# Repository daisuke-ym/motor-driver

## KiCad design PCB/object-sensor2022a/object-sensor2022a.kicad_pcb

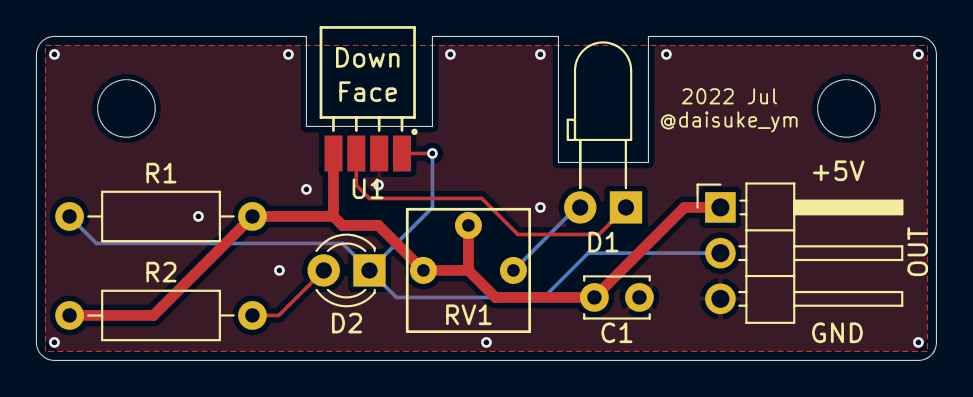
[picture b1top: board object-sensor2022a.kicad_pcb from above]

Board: 2 copper layers, 50.0 x 18.0 mm, 10 parts (0 on the bottom side), 6 nets.

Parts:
C1: 0.1u; C_Disc_D3.4mm_W2.1mm_P2.50mm
D1: IR LED; LED_D3.0mm_Horizontal_O3.81mm_Z6.0mm
D2: YELLOW; LED_D3.0mm_Clear
J1: Conn_01x03; PinHeader_1x03_P2.54mm_Horizontal
MH1, MH2: MountingHole_3.2mm_M3
R1: 10k; R_Axial_DIN0207_L6.3mm_D2.5mm_P10.16mm_Horizontal
R2: 1k; R_Axial_DIN0207_L6.3mm_D2.5mm_P10.16mm_Horizontal
RV1: 4K7; GF063P1
U1: S6809; S6809_Horizontal_Facedown

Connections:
+5V: C1.1, J1.1, R1.2, R2.1, RV1.1, RV1.2, U1.4
/WS1: D2.1, J1.2, R1.1, U1.1
GND: C1.2, J1.3, U1.2
unnamed: D1.1, U1.3
unnamed: D1.2, RV1.3
unnamed: D2.2, R2.2

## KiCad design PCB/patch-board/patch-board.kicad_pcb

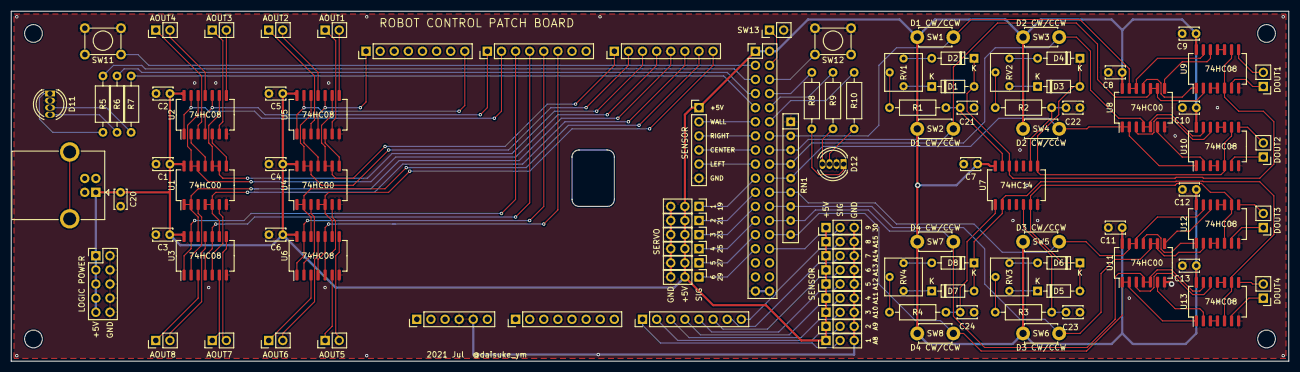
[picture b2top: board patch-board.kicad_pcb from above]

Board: 2 copper layers, 230.0 x 63.0 mm, 104 parts (0 on the bottom side), 128 nets.

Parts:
C1, C2, C3, C4, C5, C6, C7, C8, C9, C10, C11, C12, C13, C20, C21, C22, C23, C24: 0.1u; C_Disc_D3.4mm_W2.1mm_P2.50mm
D1, D2, D3, D4, D5, D6, D7, D8: 1N4148; D_DO-35_SOD27_P7.62mm_Horizontal
D11, D12: LED_RCBG; LED_D5.0mm-4_RGB
J1: USB_B; USB_B_OST_USB-B1HSxx_Horizontal
J2: LOGIC POWER SUPPLY; PinHeader_2x05_P2.54mm_Vertical
J3: MEGA_13-8; PinHeader_1x08_P2.54mm_Vertical
J4: MEGA_7-0; PinHeader_1x08_P2.54mm_Vertical
J5: MEGA_14-21; PinHeader_1x08_P2.54mm_Vertical
J6: MEGA_A8-A15; PinHeader_1x08_P2.54mm_Vertical
J7: MEGA_A0-A7; PinHeader_1x08_P2.54mm_Vertical
J8: MEGA_POWER; PinHeader_1x06_P2.54mm_Vertical
J9: MEGA_22-53; PinHeader_2x18_P2.54mm_Vertical
J11: AOUT1; PinHeader_1x02_P2.54mm_Vertical
J12: AOUT2; PinHeader_1x02_P2.54mm_Vertical
J13: AOUT3; PinHeader_1x02_P2.54mm_Vertical
J14: AOUT4; PinHeader_1x02_P2.54mm_Vertical
J15: AOUT5; PinHeader_1x02_P2.54mm_Vertical
J16: AOUT6; PinHeader_1x02_P2.54mm_Vertical
J17: AOUT7; PinHeader_1x02_P2.54mm_Vertical
J18: AOUT8; PinHeader_1x02_P2.54mm_Vertical
J21: DIGITAL OUT1; PinHeader_1x02_P2.54mm_Vertical
J22: DIGITAL OUT2; PinHeader_1x02_P2.54mm_Vertical
J23: DIGITAL OUT3; PinHeader_1x02_P2.54mm_Vertical
J24: DIGITAL OUT4; PinHeader_1x02_P2.54mm_Vertical
J31: S01; PinHeader_1x03_P2.54mm_Vertical
J32: S02; PinHeader_1x03_P2.54mm_Vertical
J33: S03; PinHeader_1x03_P2.54mm_Vertical
J34: S04; PinHeader_1x03_P2.54mm_Vertical
J35: S05; PinHeader_1x03_P2.54mm_Vertical
J36: S06; PinHeader_1x03_P2.54mm_Vertical
J37: S07; PinHeader_1x03_P2.54mm_Vertical
J38: S08; PinHeader_1x03_P2.54mm_Vertical
J39: S09; PinHeader_1x03_P2.54mm_Vertical
J40: S10; PinHeader_1x06_P2.54mm_Vertical
J41, J42, J43, J44, J45, J46: SV; PinHeader_1x03_P2.54mm_Vertical
R1, R2, R3, R4: R; R_Axial_DIN0207_L6.3mm_D2.5mm_P10.16mm_Horizontal
R5, R6, R7, R8, R9, R10: 1k; R_Axial_DIN0207_L6.3mm_D2.5mm_P10.16mm_Horizontal
RN1: 330; R_Array_SIP9
RV1, RV2, RV3, RV4: R_POT; GF063P1
SW1: D1A; TactSW_TVBP06_3.5x6.0-ThroughHole
SW2: D1B; TactSW_TVBP06_3.5x6.0-ThroughHole
SW3: D2A; TactSW_TVBP06_3.5x6.0-ThroughHole
SW4: D2B; TactSW_TVBP06_3.5x6.0-ThroughHole
SW5: D3A; TactSW_TVBP06_3.5x6.0-ThroughHole
SW6: D3B; TactSW_TVBP06_3.5x6.0-ThroughHole
SW7: D4A; TactSW_TVBP06_3.5x6.0-ThroughHole
SW8: D4B; TactSW_TVBP06_3.5x6.0-ThroughHole
SW11, SW12: SW_DPST; DTS-6-V-2
SW13: Conn_01x02; PinHeader_1x02_P2.54mm_Vertical
U1, U4, U8, U11: 74HC00; SO-14_5.3x10.2mm_P1.27mm
U2, U3, U5, U6, U9, U10, U12, U13: 74HC08; SO-14_5.3x10.2mm_P1.27mm
U7: 74HC14; SO-14_5.3x10.2mm_P1.27mm

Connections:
+5V: C1.1, C2.1, C3.1, C4.1, C5.1, C6.1, C7.1, C8.1, C9.1, C10.1, C11.1, C12.1, C13.1, C20.1, J1.1, J2.1, J2.3, J2.5, J2.7, J2.9, J9.1, J9.2, J31.1, J32.1, J33.1, J34.1, J35.1, J36.1, J37.1, J38.1, J39.1, J40.1, J41.2, J42.2, J43.2, J44.2, J45.2, J46.2, SW1.1, SW2.1, SW3.1, SW4.1, SW5.1, SW6.1, SW7.1, SW8.1, U1.14, U2.14, U3.14, U4.14, U5.14, U6.14, U7.14, U8.14, U9.14, U10.14, U11.14, U12.14, U13.14
/AOUT1A: J11.2, U5.8
/AOUT1B: J11.1, U5.6
/AOUT2A: J12.2, U5.11
/AOUT2B: J12.1, U5.3
/AOUT3A: J13.2, U2.8
/AOUT3B: J13.1, U2.6
/AOUT4A: J14.2, U2.11
/AOUT4B: J14.1, U2.3
/AOUT5A: J15.2, U3.11
/AOUT5B: J15.1, U3.3
/AOUT6A: J16.2, U3.8
/AOUT6B: J16.1, U3.6
/AOUT7A: J17.2, U6.11
/AOUT7B: J17.1, U6.3
/AOUT8A: J18.2, U6.8
/AOUT8B: J18.1, U6.6
/CSENSOR: J9.15, J40.4
/DIN1A: J9.14, RN1.2, SW1.2, U8.12, U8.13, U9.13
/DIN1B: J9.16, RN1.3, SW2.2, U8.9, U8.10, U9.2
/DIN2A: J9.18, RN1.4, SW3.2, U8.4, U8.5, U10.13
/DIN2B: J9.20, RN1.5, SW4.2, U8.1, U8.2, U10.1
/DIN3A: J9.22, RN1.6, SW5.2, U11.12, U11.13, U12.13
/DIN3B: J9.24, RN1.7, SW6.2, U11.9, U11.10, U12.2
/DIN4A: J9.26, RN1.8, SW7.2, U11.4, U11.5, U13.13
/DIN4B: J9.28, RN1.9, SW8.2, U11.1, U11.2, U13.1
/DOUT1A: J21.1, U9.6
/DOUT1B: J21.2, U9.8
/DOUT2A: J22.1, U10.6
/DOUT2B: J22.2, U10.8
/DOUT3A: J23.1, U12.6
/DOUT3B: J23.2, U12.8
/DOUT4A: J24.1, U13.6
/DOUT4B: J24.2, U13.8
/LED1B: J9.9, R7.2
/LED1G: J9.7, R6.2
/LED1R: J9.5, R5.2
/LED2B: J9.12, R10.2
/LED2G: J9.10, R9.2
/LED2R: J9.8, R8.2
/LSENSOR: J9.17, J40.5
/OSC1: D1.2, D2.1, U7.12, U9.5, U9.9
/OSC2: D3.2, D4.1, U7.8, U10.5, U10.9
/OSC3: D5.2, D6.1, U7.6, U12.5, U12.9
/OSC4: D7.2, D8.1, U7.2, U13.5, U13.9
/PWM1IN: J3.1, U5.4, U5.10
/PWM2IN: J3.8, U5.1, U5.13
/PWM3IN: J4.1, U2.4, U2.10
/PWM4IN: J4.2, U2.1, U2.13
/PWM5IN: J4.3, U3.1, U3.13
/PWM6IN: J4.4, U3.4, U3.10
/PWM7IN: J4.5, U6.1, U6.13
/PWM8IN: J4.6, U6.4, U6.10
/RSENSOR: J9.13, J40.3
/SEL1: J5.1, U4.9, U4.10, U5.9
/SEL2: J5.2, U4.12, U4.13, U5.12
/SEL3: J5.3, U1.9, U1.10, U2.9
/SEL4: J5.4, U1.12, U1.13, U2.12
/SEL5: J5.5, U1.1, U1.2, U3.12
/SEL6: J5.6, U1.4, U1.5, U3.9
/SEL7: J5.7, U4.1, U4.2, U6.12
/SEL8: J5.8, U4.4, U4.5, U6.9
/SENSOR01: J6.1, J31.2
/SENSOR02: J6.2, J32.2
/SENSOR03: J6.3, J33.2
/SENSOR04: J6.4, J34.2
/SENSOR05: J6.5, J35.2
/SENSOR06: J6.6, J36.2
/SENSOR07: J6.7, J37.2
/SENSOR08: J6.8, J38.2
/SENSOR09: J9.30, J39.2
/SV1: J9.19, J41.1
/SV2: J9.21, J42.1
/SV3: J9.23, J43.1
/SV4: J9.25, J44.1
/SV5: J9.27, J45.1
/SV6: J9.29, J46.1
/SW11: J9.3, SW11.1, SW11.3
/SW12: J9.6, SW12.1, SW12.3
/SW13: J9.4, SW13.1
/WSENSOR: J9.11, J40.2
GND: C1.2, C2.2, C3.2, C4.2, C5.2, C6.2, C7.2, C8.2, C9.2, C10.2, C11.2, C12.2, C13.2, C20.2, C21.2, C22.2, C23.2, C24.2, D11.2, D12.2, J1.4, J2.2, J2.4, J2.6, J2.8, J2.10, J8.4, J8.5, J9.35, J9.36, J31.3, J32.3, J33.3, J34.3, J35.3, J36.3, J37.3, J38.3, J39.3, J40.6, J41.3, J42.3, J43.3, J44.3, J45.3, J46.3, RN1.1, SW11.2, SW11.4, SW12.2, SW12.4, SW13.2, U1.7, U2.7, U3.7, U4.7, U5.7, U6.7, U7.3, U7.7, U7.11, U8.7, U9.7, U10.7, U11.7, U12.7, U13.7
unnamed: C21.1, R1.2, U7.13
unnamed: C22.1, R2.2, U7.9
unnamed: C23.1, R3.2, U7.5
unnamed: C24.1, R4.2, U7.1
unnamed: D1.1, RV1.1
unnamed: D2.2, RV1.3
unnamed: D3.1, RV2.1
unnamed: D4.2, RV2.3
unnamed: D5.1, RV3.1
unnamed: D6.2, RV3.3
unnamed: D7.1, RV4.1
unnamed: D8.2, RV4.3
unnamed: D11.1, R5.1
unnamed: D11.3, R7.1
unnamed: D11.4, R6.1
unnamed: D12.1, R8.1
unnamed: D12.3, R10.1
unnamed: D12.4, R9.1
unnamed: R1.1, RV1.2
unnamed: R2.1, RV2.2
unnamed: R3.1, RV3.2
unnamed: R4.1, RV4.2
unnamed: U1.3, U3.2
unnamed: U1.6, U3.5
unnamed: U1.8, U2.5
unnamed: U1.11, U2.2
unnamed: U4.3, U6.2
unnamed: U4.6, U6.5
unnamed: U4.8, U5.5
unnamed: U4.11, U5.2
unnamed: U8.8, U9.12
unnamed: U8.11, U9.1
unnamed: U9.3, U9.4
unnamed: U9.10, U9.11
unnamed: U8.6, U10.2
unnamed: U10.3, U10.4
unnamed: U10.10, U10.11
unnamed: U8.3, U10.12
unnamed: U11.3, U13.12
unnamed: U11.6, U13.2
unnamed: U11.8, U12.12
unnamed: U11.11, U12.1
unnamed: U12.3, U12.4
unnamed: U12.10, U12.11
unnamed: U13.3, U13.4
unnamed: U13.10, U13.11

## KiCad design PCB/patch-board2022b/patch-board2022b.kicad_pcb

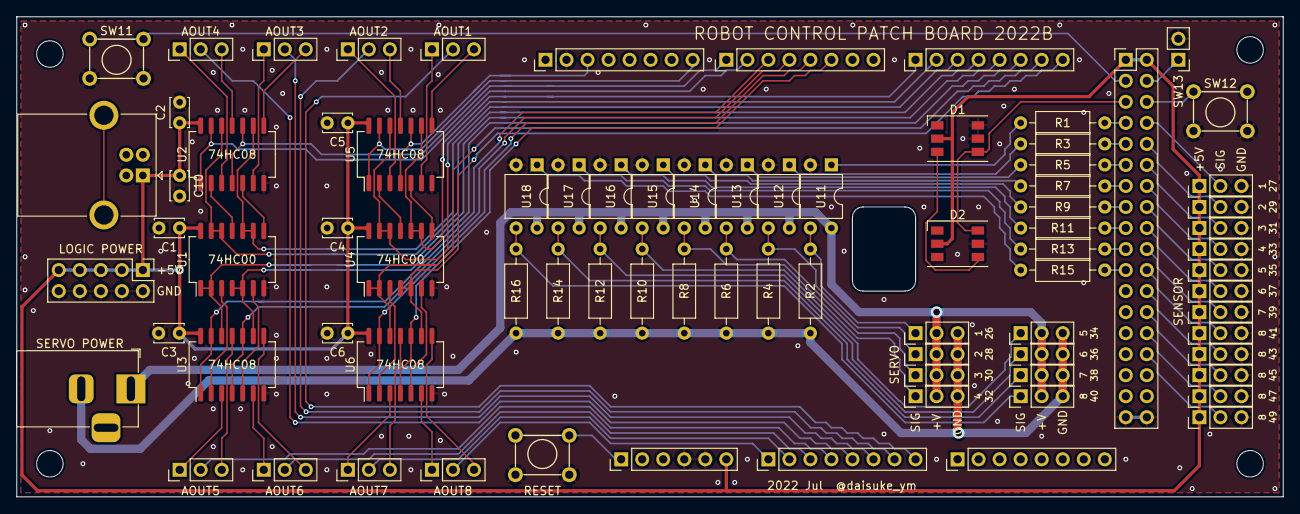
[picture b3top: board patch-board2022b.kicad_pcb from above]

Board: 2 copper layers, 153.0 x 58.0 mm, 81 parts (0 on the bottom side), 94 nets.

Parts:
C1, C2, C3, C4, C5, C6, C10: 0.1u; C_Disc_D3.4mm_W2.1mm_P2.50mm
D1, D2: WS2813; LED_WS2812_PLCC6_5.0x5.0mm_P1.6mm
J1: USB_B; USB_B_OST_USB-B1HSxx_Horizontal
J2: LOGIC POWER SUPPLY; PinHeader_2x05_P2.54mm_Vertical
J3: MEGA_13-8; PinHeader_1x08_P2.54mm_Vertical
J4: MEGA_7-0; PinHeader_1x08_P2.54mm_Vertical
J5: MEGA_14-21; PinHeader_1x08_P2.54mm_Vertical
J6: MEGA_A8-A15; PinHeader_1x08_P2.54mm_Vertical
J7: MEGA_A0-A7; PinHeader_1x08_P2.54mm_Vertical
J8: MEGA_POWER; PinHeader_1x06_P2.54mm_Vertical
J9: MEGA_22-53; PinHeader_2x18_P2.54mm_Vertical
J10: SERVO POWER SUPPLY; BarrelJack_Horizontal
J11: AOUT1; PinHeader_1x03_P2.54mm_Vertical
J12: AOUT2; PinHeader_1x03_P2.54mm_Vertical
J13: AOUT3; PinHeader_1x03_P2.54mm_Vertical
J14: AOUT4; PinHeader_1x03_P2.54mm_Vertical
J15: AOUT5; PinHeader_1x03_P2.54mm_Vertical
J16: AOUT6; PinHeader_1x03_P2.54mm_Vertical
J17: AOUT7; PinHeader_1x03_P2.54mm_Vertical
J18: AOUT8; PinHeader_1x03_P2.54mm_Vertical
J21, J22, J23, J24, J25, J26, J27, J28: SV; PinHeader_1x03_P2.54mm_Vertical
J31: S01; PinHeader_1x03_P2.54mm_Vertical
J32: S02; PinHeader_1x03_P2.54mm_Vertical
J33: S03; PinHeader_1x03_P2.54mm_Vertical
J34: S04; PinHeader_1x03_P2.54mm_Vertical
J35: S05; PinHeader_1x03_P2.54mm_Vertical
J36: S06; PinHeader_1x03_P2.54mm_Vertical
J37: S07; PinHeader_1x03_P2.54mm_Vertical
J38: S08; PinHeader_1x03_P2.54mm_Vertical
J39: S09; PinHeader_1x03_P2.54mm_Vertical
J40: S10; PinHeader_1x03_P2.54mm_Vertical
J41: S11; PinHeader_1x03_P2.54mm_Vertical
J42: S12; PinHeader_1x03_P2.54mm_Vertical
R1, R2, R3, R4, R5, R6, R7, R8, R9, R10, R11, R12, R13, R14, R15, R16: 330; R_Axial_DIN0207_L6.3mm_D2.5mm_P10.16mm_Horizontal
SW1: RESET; DTS-6-V-2
SW11, SW12: SW_DPST; DTS-6-V-2
SW13: Conn_01x02; PinHeader_1x02_P2.54mm_Vertical
U1, U4: 74HC00; SO-14_5.3x10.2mm_P1.27mm
U2, U3, U5, U6: 74HC08; SO-14_5.3x10.2mm_P1.27mm
U11, U12, U13, U14, U15, U16, U17, U18: TLP785; DIP-4_W7.62mm

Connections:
+5V: C1.1, C2.1, C3.1, C4.1, C5.1, C6.1, C10.1, D1.2, D2.2, J1.1, J2.1, J2.3, J2.5, J2.7, J2.9, J8.6, J9.1, J9.2, J31.1, J32.1, J33.1, J34.1, J35.1, J36.1, J37.1, J38.1, J39.1, J40.1, J41.1, J42.1, U1.14, U2.14, U3.14, U4.14, U5.14, U6.14
+6V: J10.1, J21.2, J22.2, J23.2, J24.2, J25.2, J26.2, J27.2, J28.2, U11.4, U12.4, U13.4, U14.4, U15.4, U16.4, U17.4, U18.4
/AOUT1A: J11.3, U5.8
/AOUT1B: J11.1, U5.6
/AOUT1M: J7.8, J11.2
/AOUT2A: J12.3, U5.11
/AOUT2B: J12.1, U5.3
/AOUT2M: J7.7, J12.2
/AOUT3A: J13.3, U2.8
/AOUT3B: J13.1, U2.6
/AOUT3M: J7.6, J13.2
/AOUT4A: J14.3, U2.11
/AOUT4B: J14.1, U2.3
/AOUT4M: J7.5, J14.2
/AOUT5A: J15.3, U3.11
/AOUT5B: J15.1, U3.3
/AOUT5M: J7.4, J15.2
/AOUT6A: J16.3, U3.8
/AOUT6B: J16.1, U3.6
/AOUT6M: J7.3, J16.2
/AOUT7A: J17.3, U6.11
/AOUT7B: J17.1, U6.3
/AOUT7M: J7.2, J17.2
/AOUT8A: J18.3, U6.8
/AOUT8B: J18.1, U6.6
/AOUT8M: J7.1, J18.2
/LED1: D1.4, D2.6, J9.5
/PWM1IN: J3.3, U5.4, U5.10
/PWM2IN: J3.8, U5.1, U5.13
/PWM3IN: J4.1, U2.4, U2.10
/PWM4IN: J4.2, U2.1, U2.13
/PWM5IN: J4.3, U3.1, U3.13
/PWM6IN: J4.4, U3.4, U3.10
/PWM7IN: J4.5, U6.1, U6.13
/PWM8IN: J4.6, U6.4, U6.10
/SEL1: J5.1, U4.9, U4.10, U5.9
/SEL2: J5.2, U4.12, U4.13, U5.12
/SEL3: J5.3, U1.9, U1.10, U2.9
/SEL4: J5.4, U1.12, U1.13, U2.12
/SEL5: J5.5, U1.1, U1.2, U3.12
/SEL6: J5.6, U1.4, U1.5, U3.9
/SEL7: J5.7, U4.1, U4.2, U6.12
/SEL8: J5.8, U4.4, U4.5, U6.9
/SENSOR1: J9.8, J31.2
/SENSOR2: J9.10, J32.2
/SENSOR3: J9.12, J33.2
/SENSOR4: J9.14, J34.2
/SENSOR5: J9.16, J35.2
/SENSOR6: J9.18, J36.2
/SENSOR7: J9.20, J37.2
/SENSOR8: J9.22, J38.2
/SENSOR9: J9.24, J39.2
/SENSOR10: J9.26, J40.2
/SENSOR11: J9.28, J41.2
/SENSOR12: J9.30, J42.2
/SV1: J21.1, R2.2, U11.3
/SV1IN: J9.7, R1.2
/SV2: J22.1, R4.2, U12.3
/SV2IN: J9.9, R3.2
/SV3: J23.1, R6.2, U13.3
/SV3IN: J9.11, R5.2
/SV4: J24.1, R8.2, U14.3
/SV4IN: J9.13, R7.2
/SV5: J25.1, R10.2, U15.3
/SV5IN: J9.15, R9.2
/SV6: J26.1, R12.2, U16.3
/SV6IN: J9.17, R11.2
/SV7: J27.1, R14.2, U17.3
/SV7IN: J9.19, R13.2
/SV8: J28.1, R16.2, U18.3
/SV8IN: J9.21, R15.2
/SW11: J9.3, SW11.1, SW11.3
/SW12: J9.6, SW12.1, SW12.3
/SW13: J9.4, SW13.1
GND: C1.2, C2.2, C3.2, C4.2, C5.2, C6.2, C10.2, D1.5, D1.6, D2.5, J1.4, J2.2, J2.4, J2.6, J2.8, J2.10, J3.2, J8.4, J8.5, J9.35, J9.36, J31.3, J32.3, J33.3, J34.3, J35.3, J36.3, J37.3, J38.3, J39.3, J40.3, J41.3, J42.3, SW1.1, SW1.3, SW11.2, SW11.4, SW12.2, SW12.4, SW13.2, U1.7, U2.7, U3.7, U4.7, U5.7, U6.7, U11.2, U12.2, U13.2, U14.2, U15.2, U16.2, U17.2, U18.2
GNDPWR: J10.2, J21.3, J22.3, J23.3, J24.3, J25.3, J26.3, J27.3, J28.3, R2.1, R4.1, R6.1, R8.1, R10.1, R12.1, R14.1, R16.1
unnamed: D1.3, D2.4
unnamed: J8.1, SW1.2, SW1.4
unnamed: R1.1, U11.1
unnamed: R3.1, U12.1
unnamed: R5.1, U13.1
unnamed: R7.1, U14.1
unnamed: R9.1, U15.1
unnamed: R11.1, U16.1
unnamed: R13.1, U17.1
unnamed: R15.1, U18.1
unnamed: U1.3, U3.2
unnamed: U1.6, U3.5
unnamed: U1.8, U2.5
unnamed: U1.11, U2.2
unnamed: U4.3, U6.2
unnamed: U4.6, U6.5
unnamed: U4.8, U5.5
unnamed: U4.11, U5.2

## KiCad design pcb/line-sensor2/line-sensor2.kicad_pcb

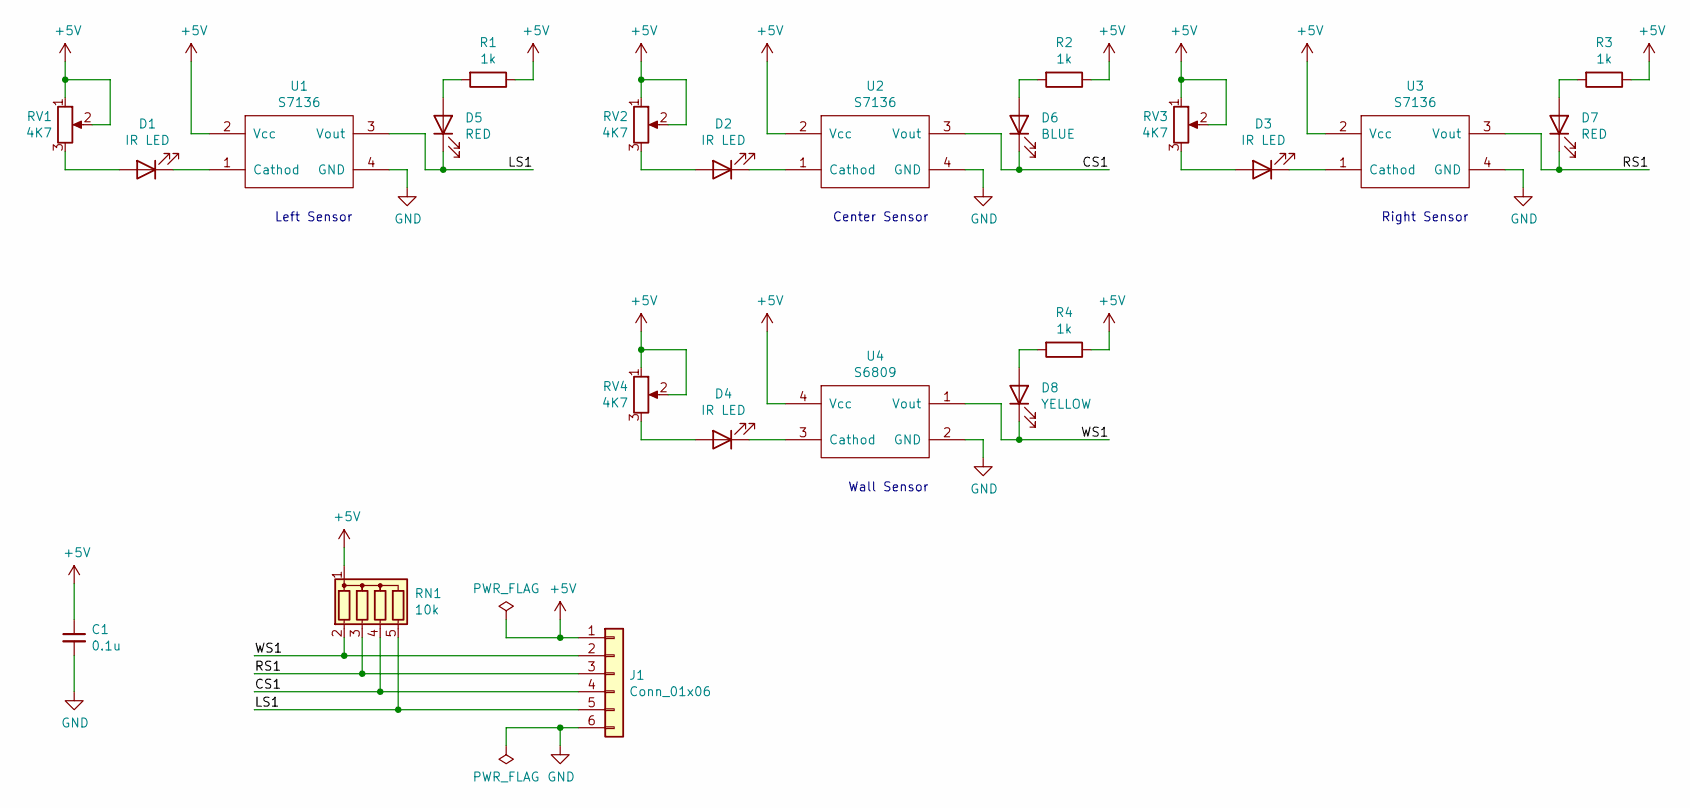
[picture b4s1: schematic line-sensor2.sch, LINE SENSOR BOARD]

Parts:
C1: 0.1u; C_Disc_D3.4mm_W2.1mm_P2.50mm
D1, D2, D3: IR LED; LED_D3.0mm_Clear
D4: IR LED; LED_D3.0mm_Horizontal_O3.81mm_Z6.0mm
D5, D7: RED; LED_D3.0mm_Clear
D6: BLUE; LED_D3.0mm_Clear
D8: YELLOW; LED_D3.0mm_Clear
J1: Conn_01x06; PinHeader_1x06_P2.54mm_Horizontal
R1, R2, R3, R4: 1k; R_Axial_DIN0207_L6.3mm_D2.5mm_P10.16mm_Horizontal
RN1: 10k; R_Array_SIP5
RV1, RV2, RV3, RV4: 4K7; GF063P1
U1, U2, U3: S7136
U4: S6809; S6809_Horizontal_Facedown

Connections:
+5V: C1.1, J1.1, R1.1, R2.1, R3.1, R4.1, RN1.1 (common), RV1.1, RV1.2, RV2.1, RV2.2, RV3.1, RV3.2, RV4.1, RV4.2, U1.2 (Vcc), U2.2 (Vcc), U3.2 (Vcc), U4.4 (Vcc)
/CS1: D6.1 (K), J1.4, RN1.4 (R3), U2.3 (Vout)
/LS1: D5.1 (K), J1.5, RN1.5 (R4), U1.3 (Vout)
/RS1: D7.1 (K), J1.3, RN1.3 (R2), U3.3 (Vout)
/WS1: D8.1 (K), J1.2, RN1.2 (R1), U4.1 (Vout)
GND: C1.2, J1.6, U1.4 (GND), U2.4 (GND), U3.4 (GND), U4.2 (GND)
unnamed: D1.1 (K), U1.1 (Cathod)
unnamed: D1.2 (A), RV1.3
unnamed: D2.1 (K), U2.1 (Cathod)
unnamed: D2.2 (A), RV2.3
unnamed: D3.1 (K), U3.1 (Cathod)
unnamed: D3.2 (A), RV3.3
unnamed: D4.1 (K), U4.3 (Cathod)
unnamed: D4.2 (A), RV4.3
unnamed: D5.2 (A), R1.2
unnamed: D6.2 (A), R2.2
unnamed: D7.2 (A), R3.2
unnamed: D8.2 (A), R4.2

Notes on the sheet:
Wall Sensor
Left Sensor
Center Sensor
Right Sensor

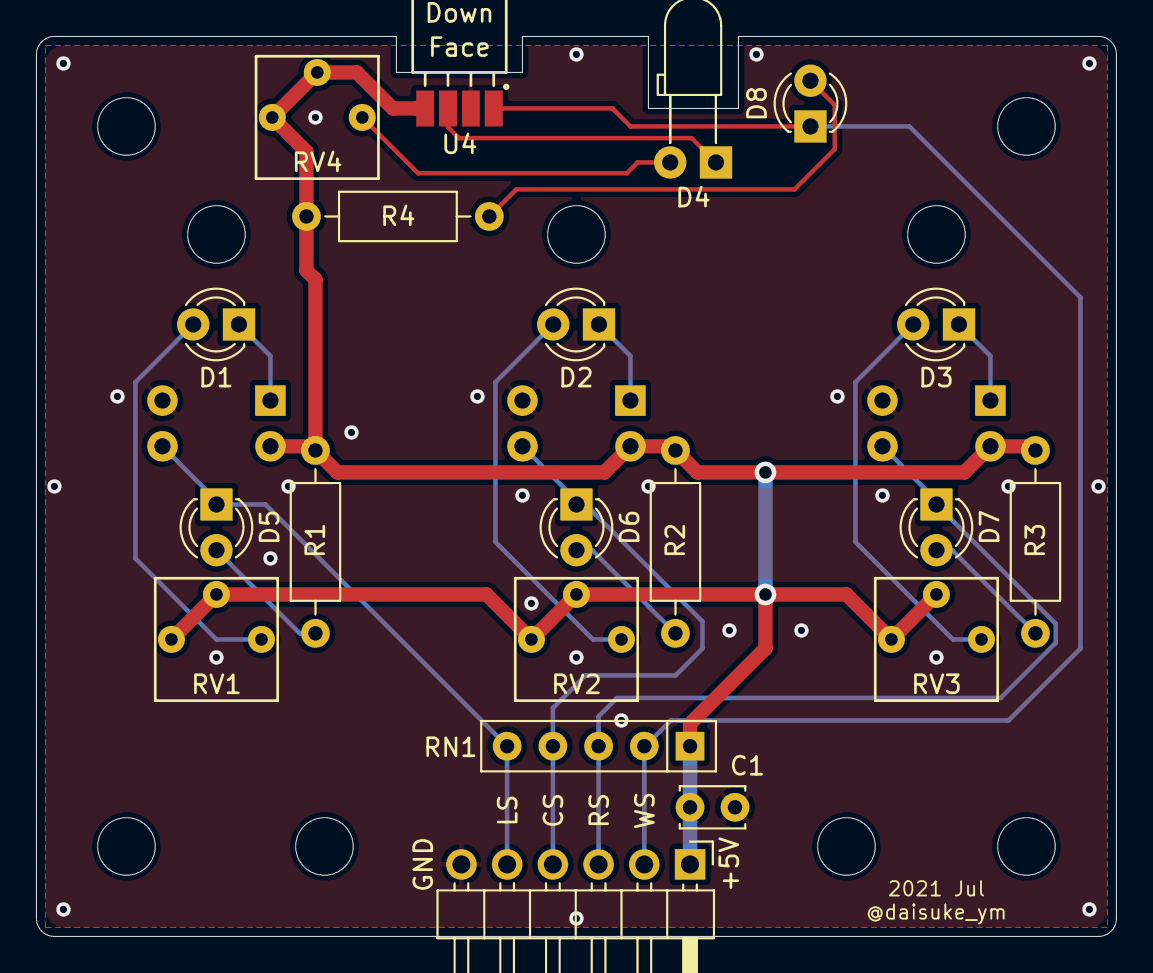
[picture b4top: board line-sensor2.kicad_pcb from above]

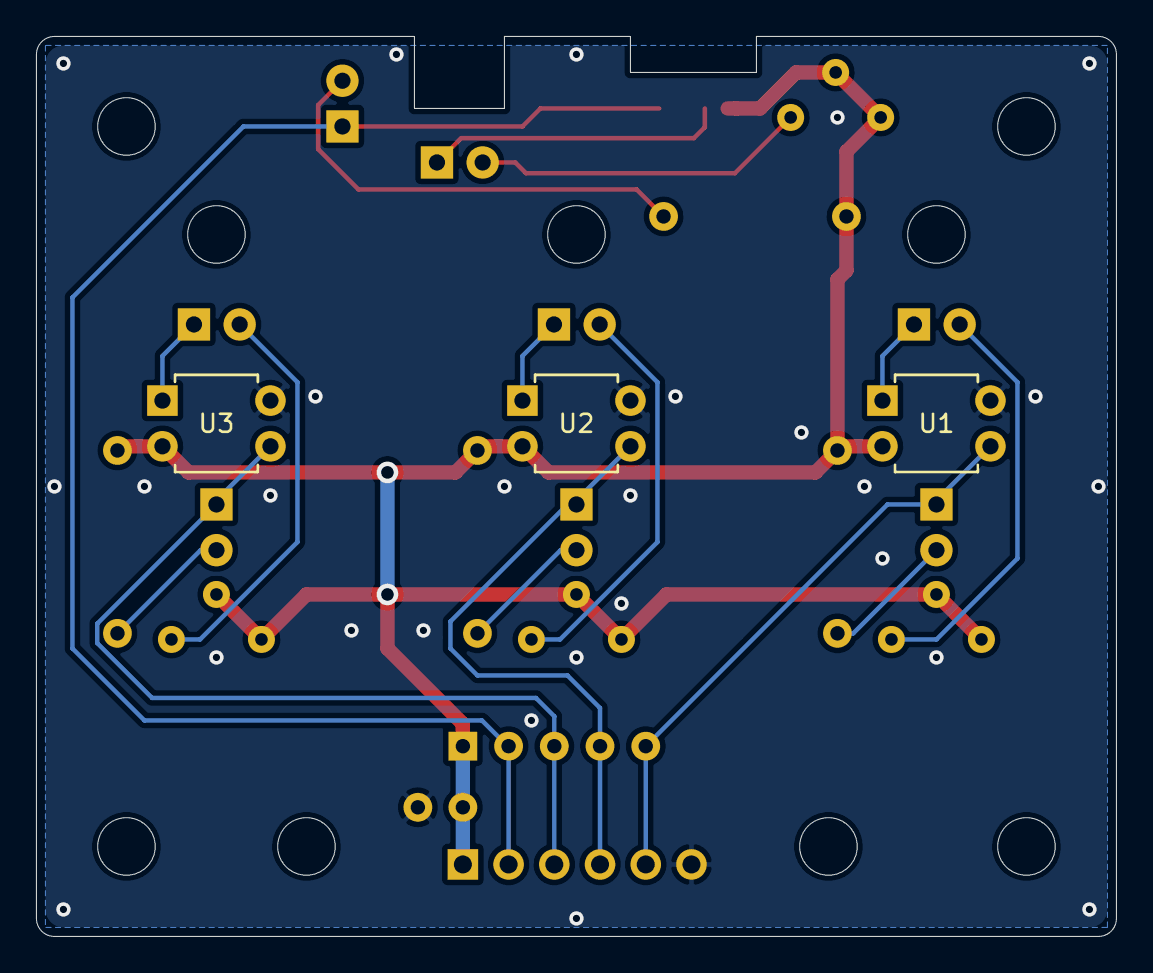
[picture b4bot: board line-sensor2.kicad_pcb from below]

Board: 2 copper layers, 60.0 x 50.0 mm, 32 parts (3 on the bottom side), 18 nets.

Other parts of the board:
MH1, MH2, MH3, MH4, MH5, MH6, MH8, MH9, MH10: MountingHole_3.2mm_M3

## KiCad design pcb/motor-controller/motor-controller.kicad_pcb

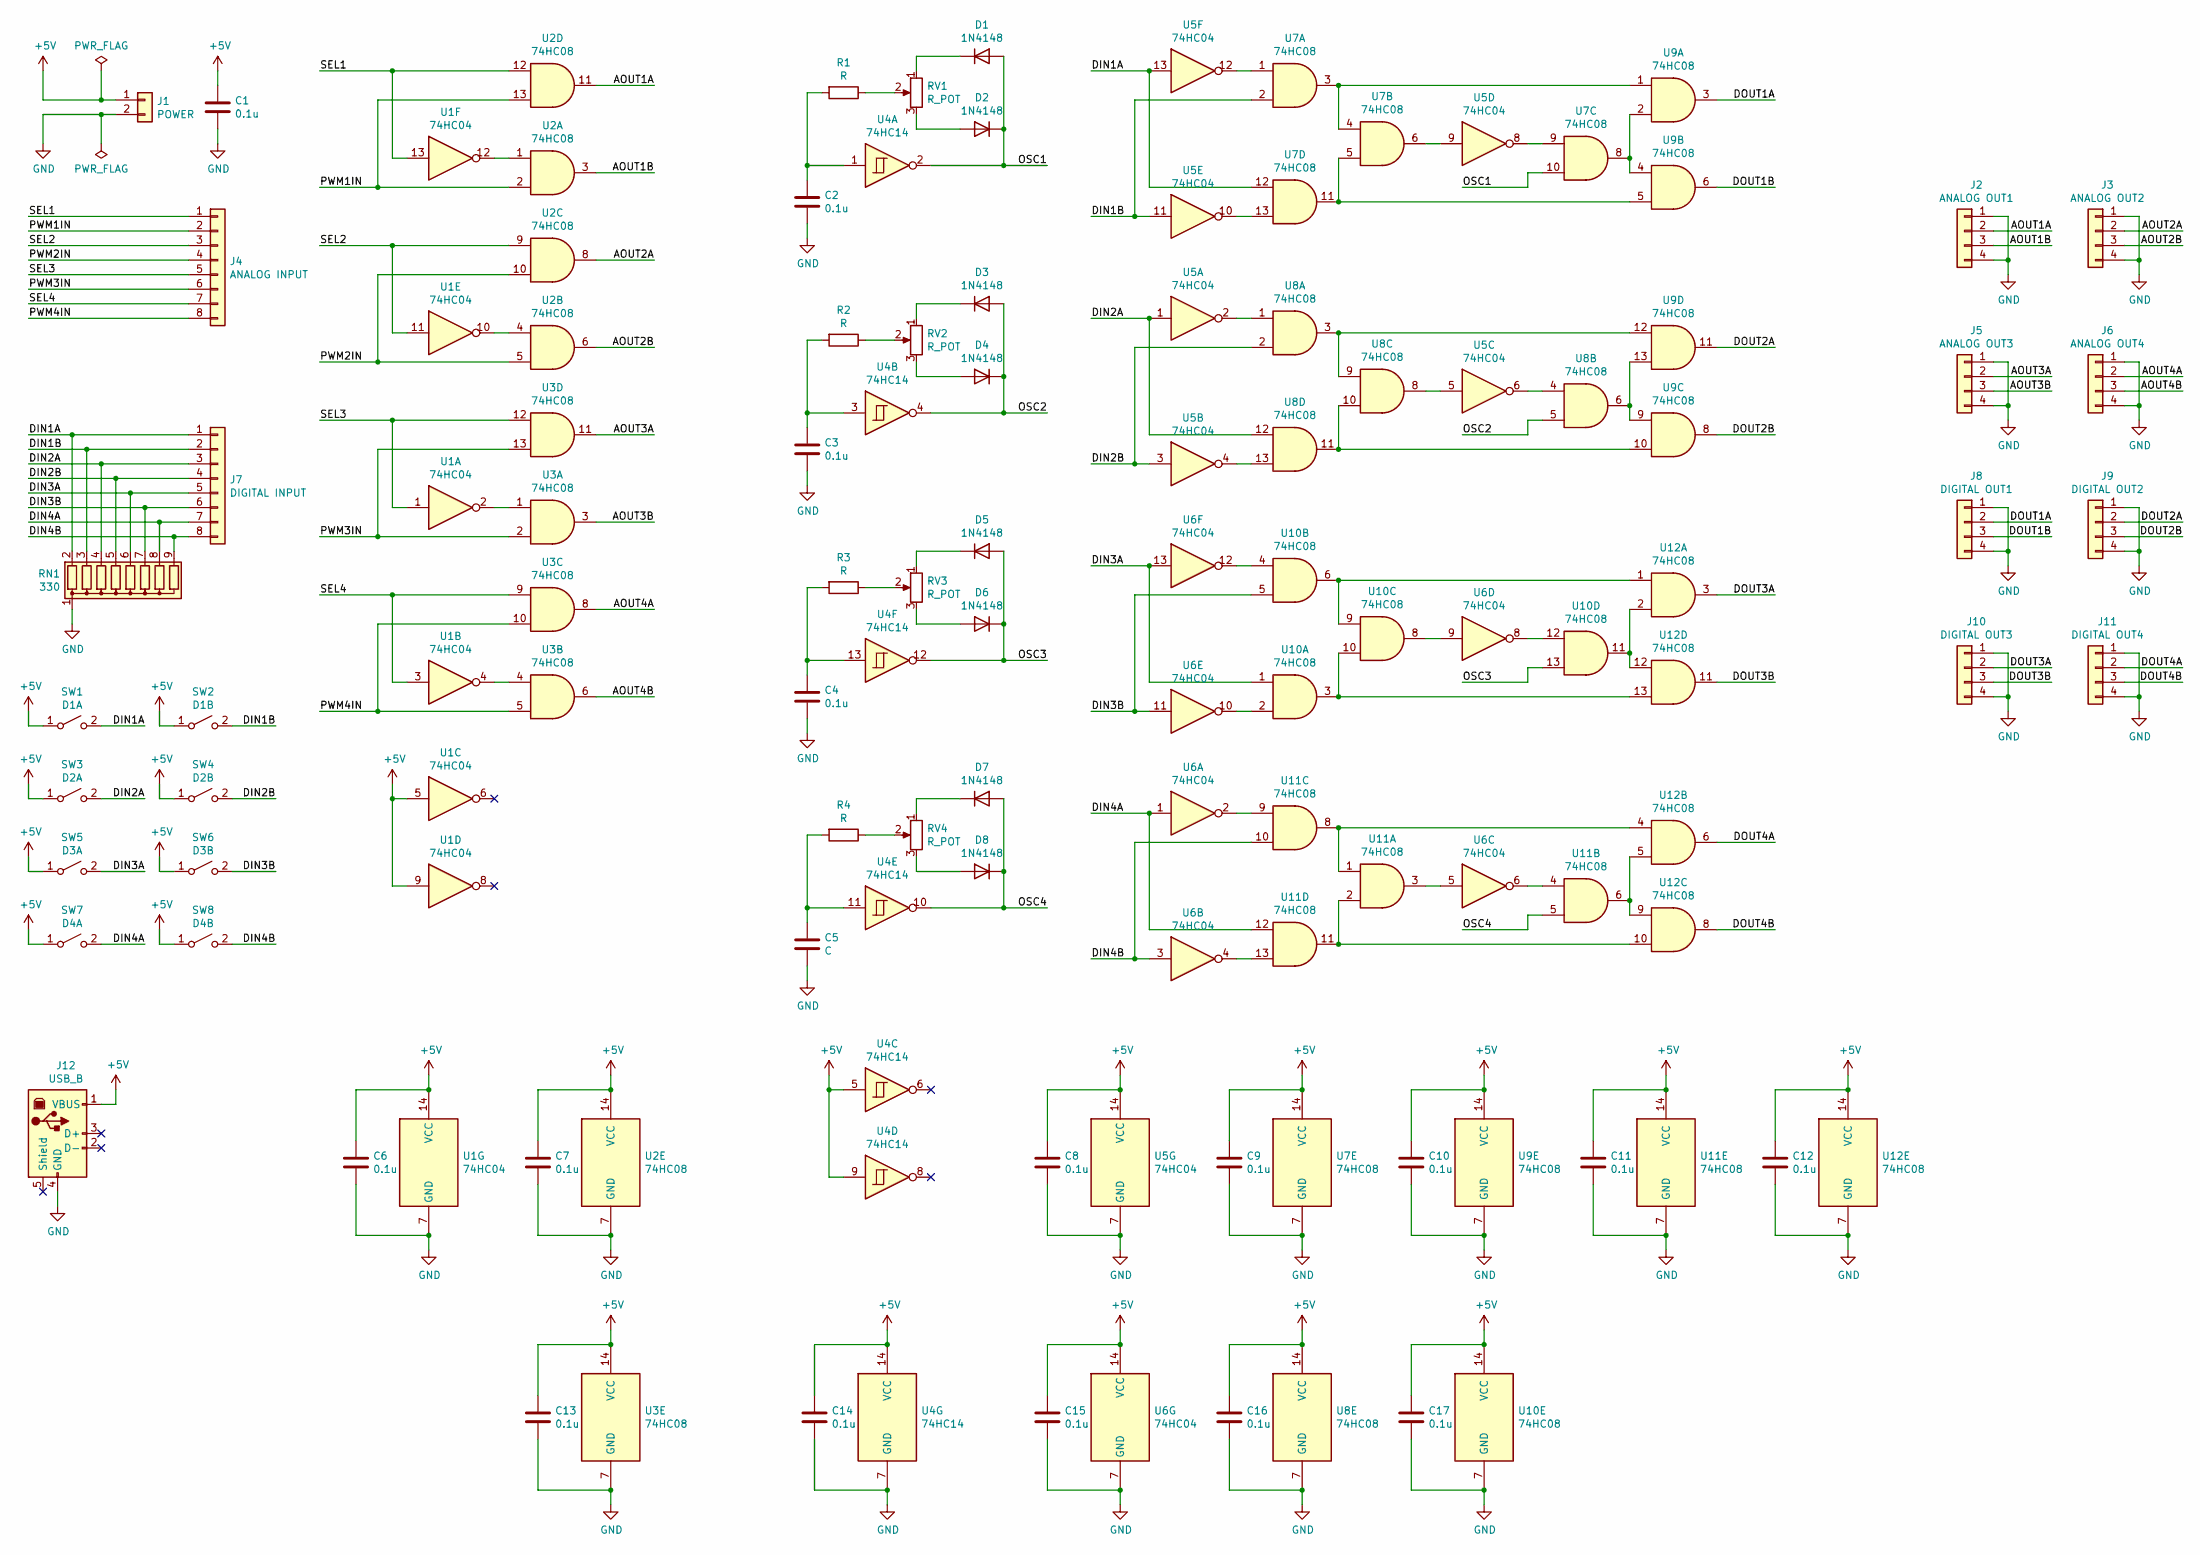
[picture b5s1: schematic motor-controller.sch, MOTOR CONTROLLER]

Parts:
C1, C2, C3, C4, C6, C7, C8, C9, C10, C11, C12, C13, C14, C15, C16, C17: 0.1u; C_Disc_D3.4mm_W2.1mm_P2.50mm
C5: C; C_Disc_D3.4mm_W2.1mm_P2.50mm
D1, D2, D3, D4, D5, D6, D7, D8: 1N4148; D_DO-35_SOD27_P7.62mm_Horizontal
J1: POWER; PinHeader_1x02_P2.54mm_Vertical
J2: ANALOG OUT1; PinHeader_1x04_P2.54mm_Vertical
J3: ANALOG OUT2; PinHeader_1x04_P2.54mm_Vertical
J4: ANALOG INPUT; PinHeader_1x08_P2.54mm_Vertical
J5: ANALOG OUT3; PinHeader_1x04_P2.54mm_Vertical
J6: ANALOG OUT4; PinHeader_1x04_P2.54mm_Vertical
J7: DIGITAL INPUT; PinHeader_1x08_P2.54mm_Vertical
J8: DIGITAL OUT1; PinHeader_1x04_P2.54mm_Vertical
J9: DIGITAL OUT2; PinHeader_1x04_P2.54mm_Vertical
J10: DIGITAL OUT3; PinHeader_1x04_P2.54mm_Vertical
J11: DIGITAL OUT4; PinHeader_1x04_P2.54mm_Vertical
J12: USB_B; USB_B_OST_USB-B1HSxx_Horizontal
R1, R2, R3, R4: R; R_Axial_DIN0207_L6.3mm_D2.5mm_P10.16mm_Horizontal
RN1: 330; R_Array_SIP9
RV1, RV2, RV3, RV4: R_POT; TSR-065
SW1: D1A; TactSW_TVBP06_3.5x6.0-ThroughHole
SW2: D1B; TactSW_TVBP06_3.5x6.0-ThroughHole
SW3: D2A; TactSW_TVBP06_3.5x6.0-ThroughHole
SW4: D2B; TactSW_TVBP06_3.5x6.0-ThroughHole
SW5: D3A; TactSW_TVBP06_3.5x6.0-ThroughHole
SW6: D3B; TactSW_TVBP06_3.5x6.0-ThroughHole
SW7: D4A; TactSW_TVBP06_3.5x6.0-ThroughHole
SW8: D4B; TactSW_TVBP06_3.5x6.0-ThroughHole
U1, U5, U6: 74HC04; DIP-14_W7.62mm_Socket
U2, U3, U7, U8, U9, U10, U11, U12: 74HC08; DIP-14_W7.62mm_Socket
U4: 74HC14; DIP-14_W7.62mm_Socket

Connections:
+5V: C1.1, C6.1, C7.1, C8.1, C9.1, C10.1, C11.1, C12.1, C13.1, C14.1, C15.1, C16.1, C17.1, J1.1, J12.1 (VBUS), SW1.1 (A), SW2.1 (A), SW3.1 (A), SW4.1 (A), SW5.1 (A), SW6.1 (A), SW7.1 (A), SW8.1 (A), U1.5, U1.9, U1.14 (VCC), U2.14 (VCC), U3.14 (VCC), U4.5, U4.9, U4.14 (VCC), U5.14 (VCC), U6.14 (VCC), U7.14 (VCC), U8.14 (VCC), U9.14 (VCC), U10.14 (VCC), U11.14 (VCC), U12.14 (VCC)
/AOUT1A: J2.2, U2.11
/AOUT1B: J2.3, U2.3
/AOUT2A: J3.2, U2.8
/AOUT2B: J3.3, U2.6
/AOUT3A: J5.2, U3.11
/AOUT3B: J5.3, U3.3
/AOUT4A: J6.2, U3.8
/AOUT4B: J6.3, U3.6
/DIN1A: J7.1, RN1.2 (R1), SW1.2 (B), U5.13, U7.12
/DIN1B: J7.2, RN1.3 (R2), SW2.2 (B), U5.11, U7.2
/DIN2A: J7.3, RN1.4 (R3), SW3.2 (B), U5.1, U8.12
/DIN2B: J7.4, RN1.5 (R4), SW4.2 (B), U5.3, U8.2
/DIN3A: J7.5, RN1.6 (R5), SW5.2 (B), U6.13, U10.1
/DIN3B: J7.6, RN1.7 (R6), SW6.2 (B), U6.11, U10.5
/DIN4A: J7.7, RN1.8 (R7), SW7.2 (B), U6.1, U11.12
/DIN4B: J7.8, RN1.9 (R8), SW8.2 (B), U6.3, U11.10
/DOUT1A: J8.2, U9.3
/DOUT1B: J8.3, U9.6
/DOUT2A: J9.2, U9.11
/DOUT2B: J9.3, U9.8
/DOUT3A: J10.2, U12.3
/DOUT3B: J10.3, U12.11
/DOUT4A: J11.2, U12.6
/DOUT4B: J11.3, U12.8
/OSC1: D1.2 (A), D2.1 (K), U4.2, U7.10
/OSC2: D3.2 (A), D4.1 (K), U4.4, U8.5
/OSC3: D5.2 (A), D6.1 (K), U4.12, U10.13
/OSC4: D7.2 (A), D8.1 (K), U4.10, U11.5
/PWM1IN: J4.2, U2.2, U2.13
/PWM2IN: J4.4, U2.5, U2.10
/PWM3IN: J4.6, U3.2, U3.13
/PWM4IN: J4.8, U3.5, U3.10
/SEL1: J4.1, U1.13, U2.12
/SEL2: J4.3, U1.11, U2.9
/SEL3: J4.5, U1.1, U3.12
/SEL4: J4.7, U1.3, U3.9
GND: C1.2, C2.2, C3.2, C4.2, C5.2, C6.2, C7.2, C8.2, C9.2, C10.2, C11.2, C12.2, C13.2, C14.2, C15.2, C16.2, C17.2, J1.2, J2.1, J2.4, J3.1, J3.4, J5.1, J5.4, J6.1, J6.4, J8.1, J8.4, J9.1, J9.4, J10.1, J10.4, J11.1, J11.4, J12.4 (GND), RN1.1 (common), U1.7 (GND), U2.7 (GND), U3.7 (GND), U4.7 (GND), U5.7 (GND), U6.7 (GND), U7.7 (GND), U8.7 (GND), U9.7 (GND), U10.7 (GND), U11.7 (GND), U12.7 (GND)
unnamed: C2.1, R1.2, U4.1
unnamed: C3.1, R2.2, U4.3
unnamed: C4.1, R3.2, U4.13
unnamed: C5.1, R4.2, U4.11
unnamed: D1.1 (K), RV1.1
unnamed: D2.2 (A), RV1.3
unnamed: D3.1 (K), RV2.1
unnamed: D4.2 (A), RV2.3
unnamed: D5.1 (K), RV3.1
unnamed: D6.2 (A), RV3.3
unnamed: D7.1 (K), RV4.1
unnamed: D8.2 (A), RV4.3
unnamed: R1.1, RV1.2
unnamed: R2.1, RV2.2
unnamed: R3.1, RV3.2
unnamed: R4.1, RV4.2
unnamed: U1.2, U3.1
unnamed: U1.4, U3.4
unnamed: U1.10, U2.4
unnamed: U1.12, U2.1
unnamed: U5.2, U8.1
unnamed: U5.4, U8.13
unnamed: U5.5, U8.8
unnamed: U5.6, U8.4
unnamed: U5.8, U7.9
unnamed: U5.9, U7.6
unnamed: U5.10, U7.13
unnamed: U5.12, U7.1
unnamed: U7.3, U7.4, U9.1
unnamed: U7.8, U9.2, U9.4
unnamed: U7.5, U7.11, U9.5
unnamed: U8.3, U8.9, U9.12
unnamed: U8.6, U9.9, U9.13
unnamed: U8.10, U8.11, U9.10
unnamed: U6.10, U10.2
unnamed: U6.12, U10.4
unnamed: U10.6, U10.9, U12.1
unnamed: U6.9, U10.8
unnamed: U10.3, U10.10, U12.13
unnamed: U10.11, U12.2, U12.12
unnamed: U6.8, U10.12
unnamed: U11.1, U11.8, U12.4
unnamed: U6.5, U11.3
unnamed: U6.6, U11.4
unnamed: U11.6, U12.5, U12.9
unnamed: U6.2, U11.9
unnamed: U11.2, U11.11, U12.10
unnamed: U6.4, U11.13

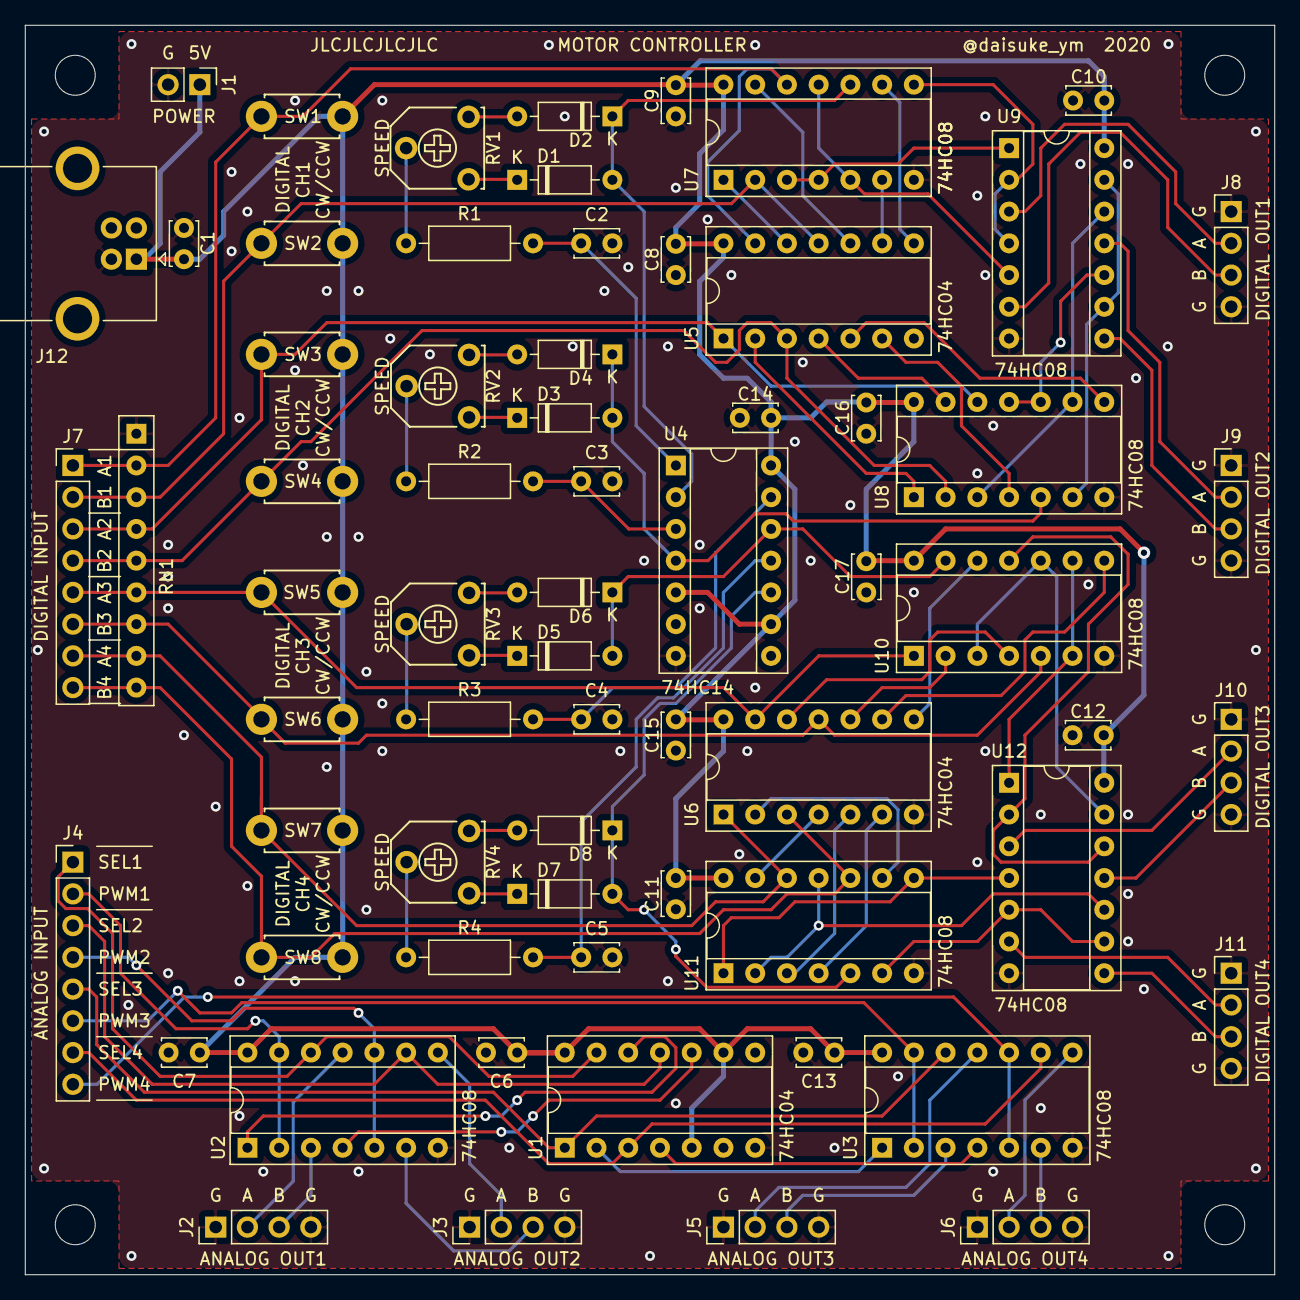
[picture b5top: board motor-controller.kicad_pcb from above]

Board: 2 copper layers, 100.0 x 100.0 mm, 70 parts (0 on the bottom side), 86 nets.

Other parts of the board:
MH1, MH2, MH3, MH4: MountingHole_3.2mm_M3
